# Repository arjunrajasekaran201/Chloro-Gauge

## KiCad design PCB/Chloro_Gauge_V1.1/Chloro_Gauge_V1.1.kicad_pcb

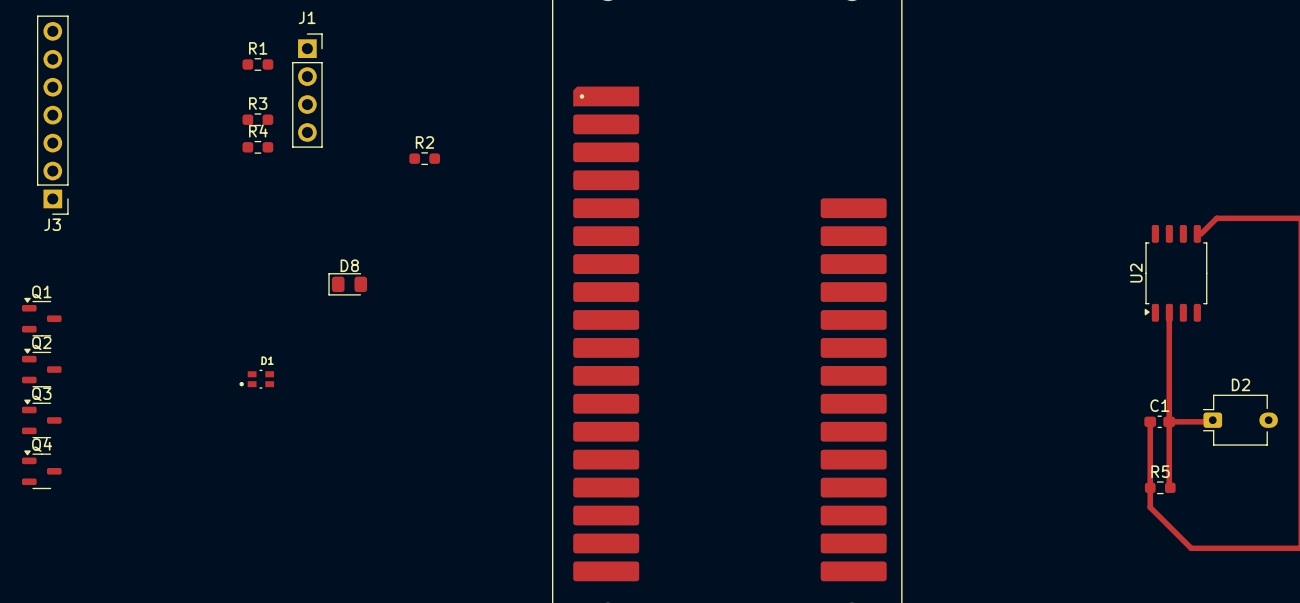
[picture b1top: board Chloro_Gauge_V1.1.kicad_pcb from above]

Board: 2 copper layers, 17 parts (0 on the bottom side), 19 nets.

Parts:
C1: 100nF; C_0603_1608Metric_Pad1.08x0.95mm_HandSolder
D1: Everlight_RGB_19-237_R6GHBHC-A01_2T; LED_19-237_R6GHBHC-A01_2T
D2: BPW34; Osram_DIL2_4.3x4.65mm_P5.08mm
D8: NIR; LED_0805_2012Metric_Pad1.15x1.40mm_HandSolder
J1: DISPLAY; PinSocket_1x04_P2.54mm_Vertical
J3: COLOUR SENSOR; PinHeader_1x07_P2.54mm_Vertical
Q1, Q2, Q3, Q4: BC547; SOT-23-3
R1, R2, R3, R4: 1k; R_0603_1608Metric_Pad0.98x0.95mm_HandSolder
R5: 10k; R_0603_1608Metric_Pad0.98x0.95mm_HandSolder
U1: DFR0654; MODULE_DFR0654
U2: UA741CN; SOIC-8_5.3x5.3mm_P1.27mm

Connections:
+3.3V: D1.4, D8.2 (A), J1.2, J3.5, U1.2 (3.3V), U1.31 (3.3V), U2.3 (V+)
BLUE_D10: R3.1, U1.21 (D12)
CLRSNS_INT_D9: J3.2, U1.11 (D9)
GND: D2.2 (A), J1.1, J3.6, Q1.3 (E), Q2.3 (E), Q3.3 (E), Q4.3 (E), U1.4 (GND), U1.30 (GND), U2.1 (+), U2.4 (V-)
GREEN_D11: R2.1, U1.20 (D11)
NIR_D13: R4.2, U1.22 (D13)
unnamed: C1.2, D2.1 (K), R5.2, U2.2 (-)
unnamed: D8.1 (K), Q4.1 (C)
unnamed: Q1.2 (B), R1.2
unnamed: D1.1, Q1.1 (C)
unnamed: Q2.2 (B), R2.2
unnamed: D1.2, Q2.1 (C)
unnamed: Q3.2 (B), R3.2
unnamed: D1.3, Q3.1 (C)
unnamed: Q4.2 (B), R4.1
PHOTODIODE_ADC_A0: C1.1, R5.1, U1.23 (A0), U2.5
RED_D12: R1.1, U1.19 (D10)
SCL: J1.3, J3.4, U1.9 (SCL), U1.29 (SCL)
SDA: J1.4, J3.3, U1.10 (SDA), U1.28 (SDA)

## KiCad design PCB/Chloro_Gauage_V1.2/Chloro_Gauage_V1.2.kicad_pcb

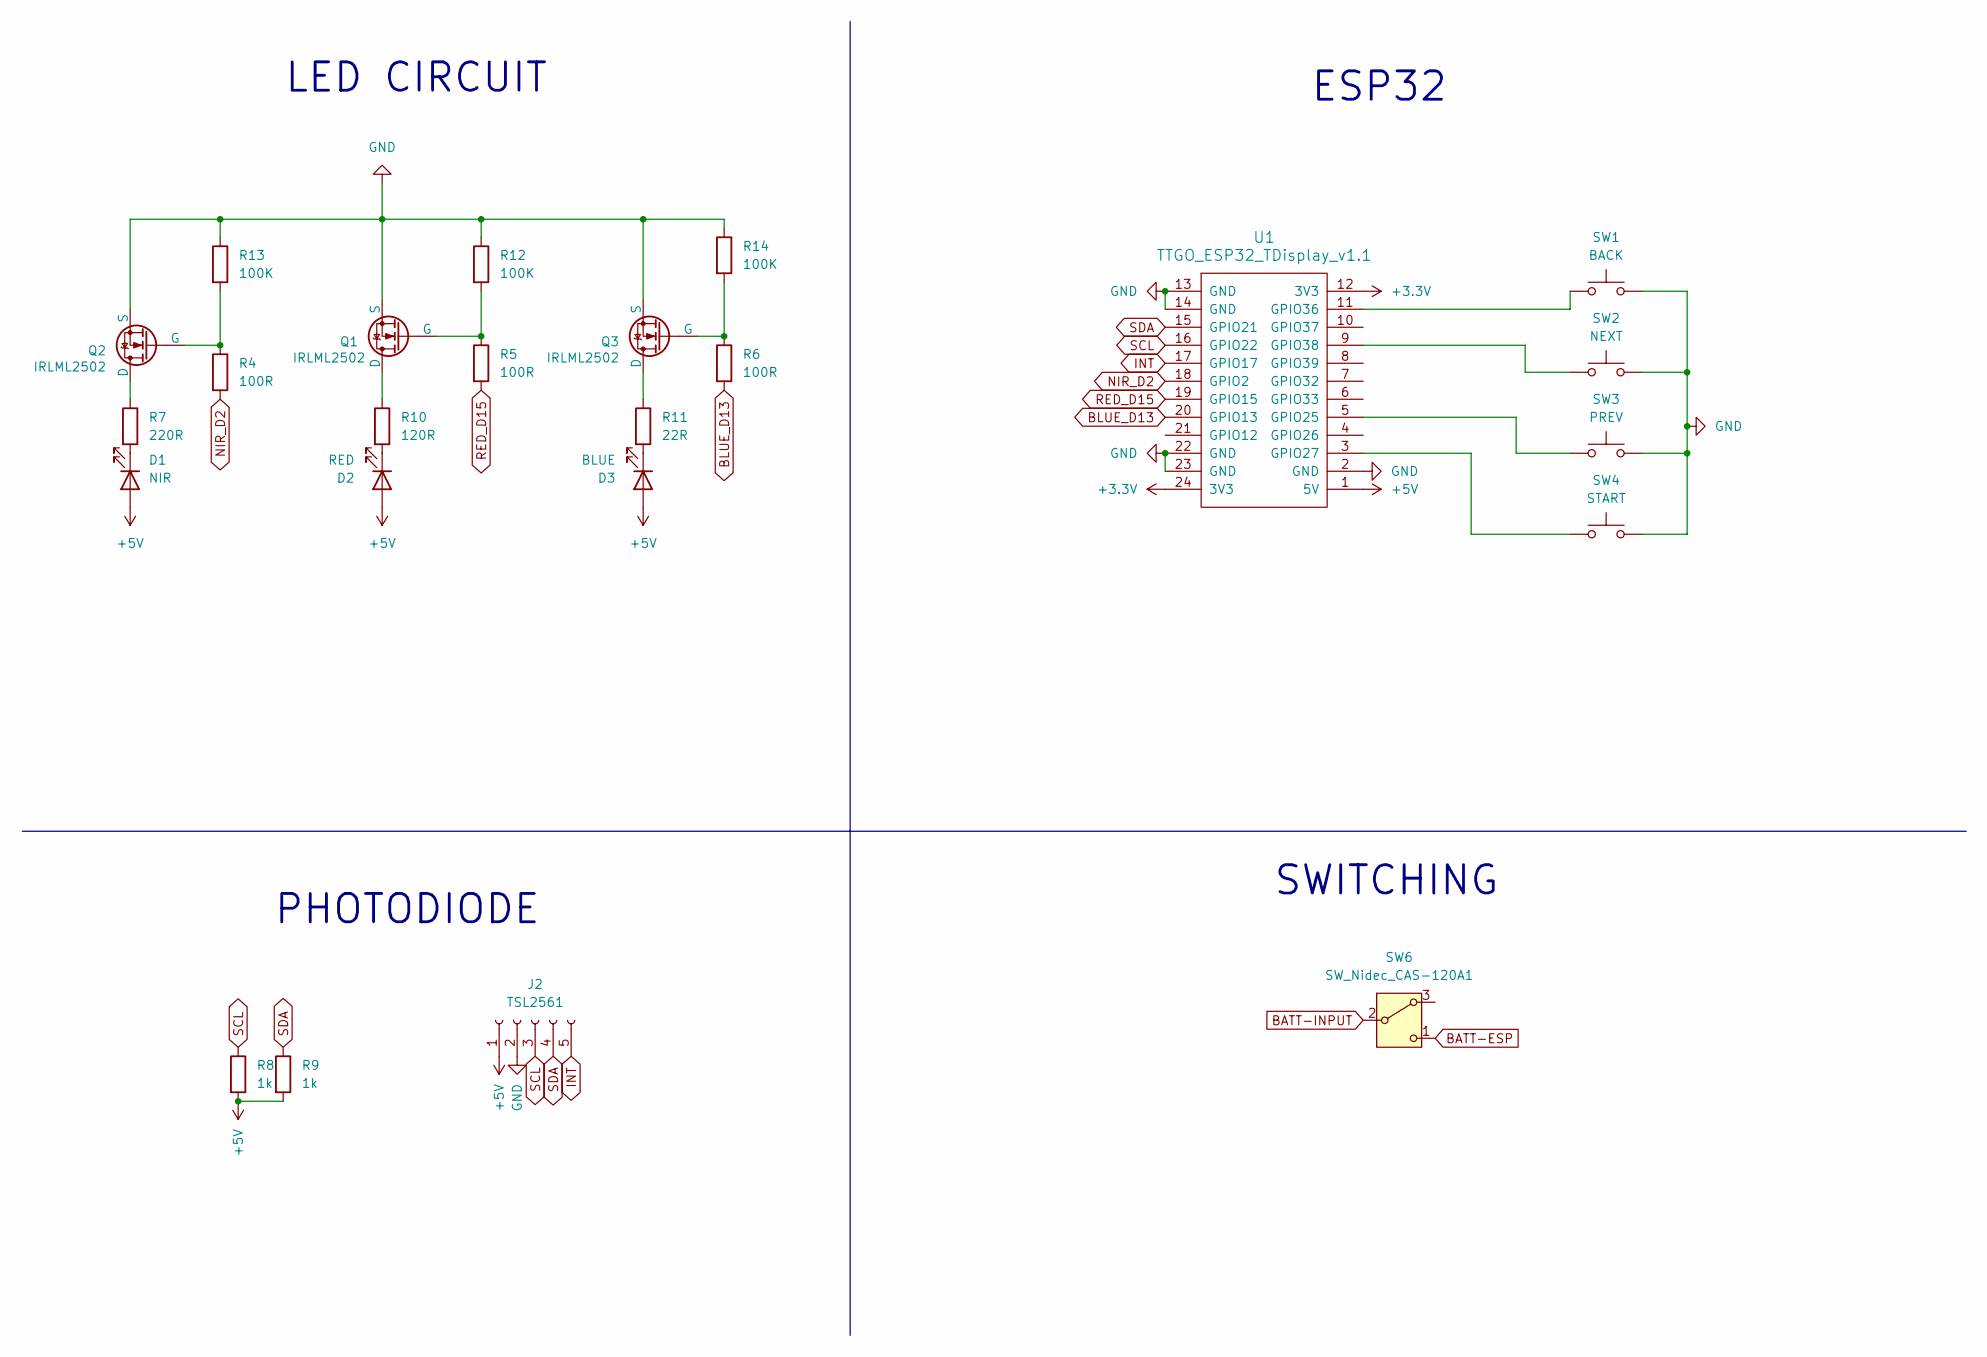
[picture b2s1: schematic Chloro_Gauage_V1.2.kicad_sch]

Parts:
D1: NIR; LED_0805_2012Metric_Pad1.15x1.40mm_HandSolder
D2: RED; LED_1206_3216Metric_Pad1.42x1.75mm_HandSolder
D3: BLUE; LED_1206_3216Metric_Pad1.42x1.75mm_HandSolder
J2: TSL2561; PinSocket_1x05_P2.54mm_Vertical
Q1, Q2, Q3: IRLML2502; TSOT-23
R4, R5, R6: 100R; R_1206_3216Metric_Pad1.30x1.75mm_HandSolder
R7: 220R; R_1206_3216Metric_Pad1.30x1.75mm_HandSolder
R8, R9: 1k; R_1206_3216Metric_Pad1.30x1.75mm_HandSolder
R10: 120R; R_1206_3216Metric_Pad1.30x1.75mm_HandSolder
R11: 22R; R_1206_3216Metric_Pad1.30x1.75mm_HandSolder
R12, R13, R14: 100K; R_1206_3216Metric_Pad1.30x1.75mm_HandSolder
SW1: BACK; SW_SPST_Omron_B3FS-105xP
SW2: NEXT; SW_SPST_Omron_B3FS-105xP
SW3: PREV; SW_SPST_Omron_B3FS-105xP
SW4: START; SW_SPST_Omron_B3FS-105xP
SW6: SW_Nidec_CAS-120A1; SW_DIP_SPSTx01_Slide_Copal_CVS-01xB_W5.9mm_P1mm
U1: TTGO_ESP32_TDisplay_v1.1

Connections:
+3.3V: U1.12 (3V3), U1.24 (3V3)
+5V: D1.2 (A), D2.2 (A), D3.2 (A), J2.1, R8.2, R9.2, U1.1 (5V)
BATT-ESP: SW6.1 (C)
BATT-INPUT: SW6.2 (B)
BLUE_D13: R6.2, U1.20 (GPIO13)
GND: J2.2, Q1.2 (S), Q2.2 (S), Q3.2 (S), R12.1, R13.1, R14.1, SW1.2, SW2.2, SW3.2, SW4.2, U1.2 (GND), U1.13 (GND), U1.14 (GND), U1.22 (GND), U1.23 (GND)
INT: J2.5, U1.17 (GPIO17)
NIR_D2: R4.2, U1.18 (GPIO2)
unnamed: D1.1 (K), R7.2
unnamed: D2.1 (K), R10.2
unnamed: D3.1 (K), R11.2
unnamed: Q1.3 (D), R10.1
unnamed: Q1.1 (G), R5.1, R12.2
unnamed: Q2.3 (D), R7.1
unnamed: Q2.1 (G), R4.1, R13.2
unnamed: Q3.3 (D), R11.1
unnamed: Q3.1 (G), R6.1, R14.2
unnamed: SW3.1, U1.5 (GPIO25)
unnamed: SW4.1, U1.3 (GPIO27)
unnamed: SW1.1, U1.11 (GPIO36)
unnamed: SW2.1, U1.9 (GPIO38)
RED_D15: R5.2, U1.19 (GPIO15)
SCL: J2.3, R8.1, U1.16 (GPIO22)
SDA: J2.4, R9.1, U1.15 (GPIO21)

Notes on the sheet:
SWITCHING
PHOTODIODE
LED CIRCUIT
ESP32

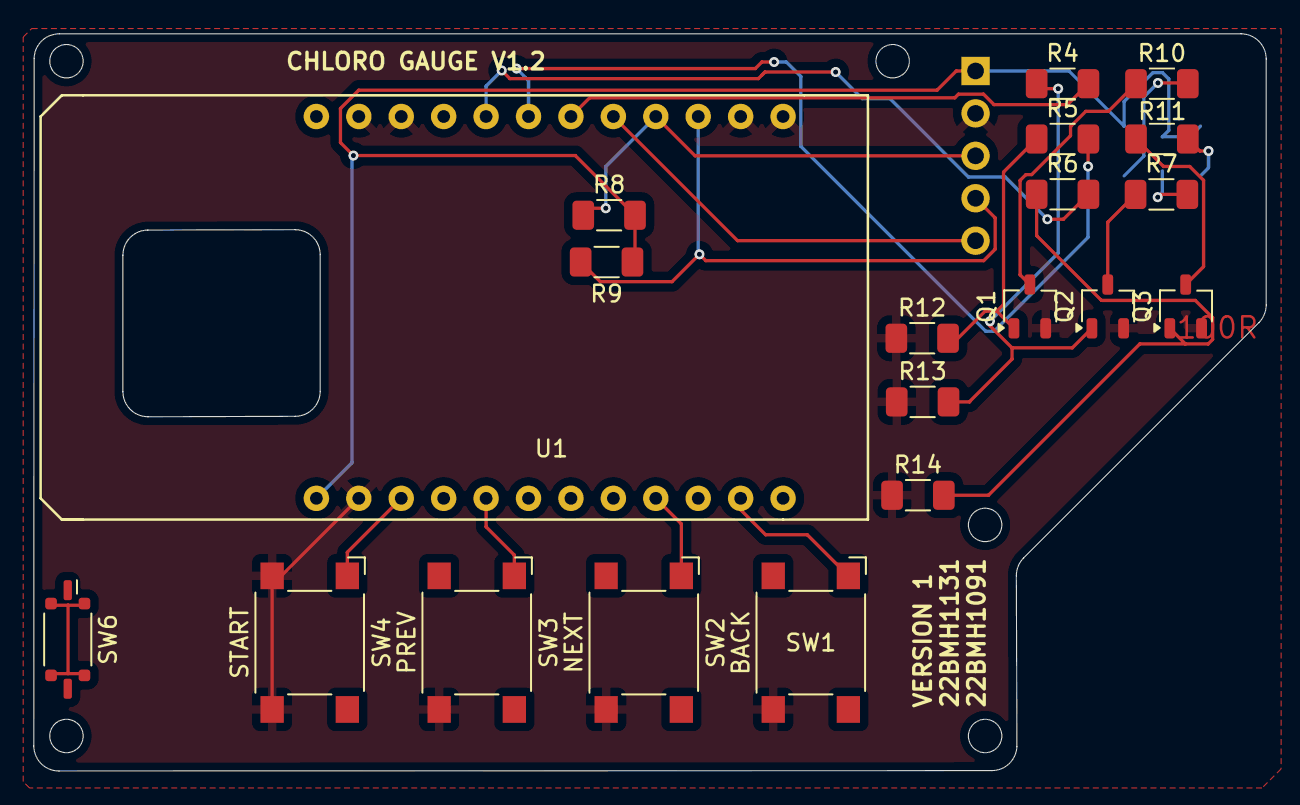
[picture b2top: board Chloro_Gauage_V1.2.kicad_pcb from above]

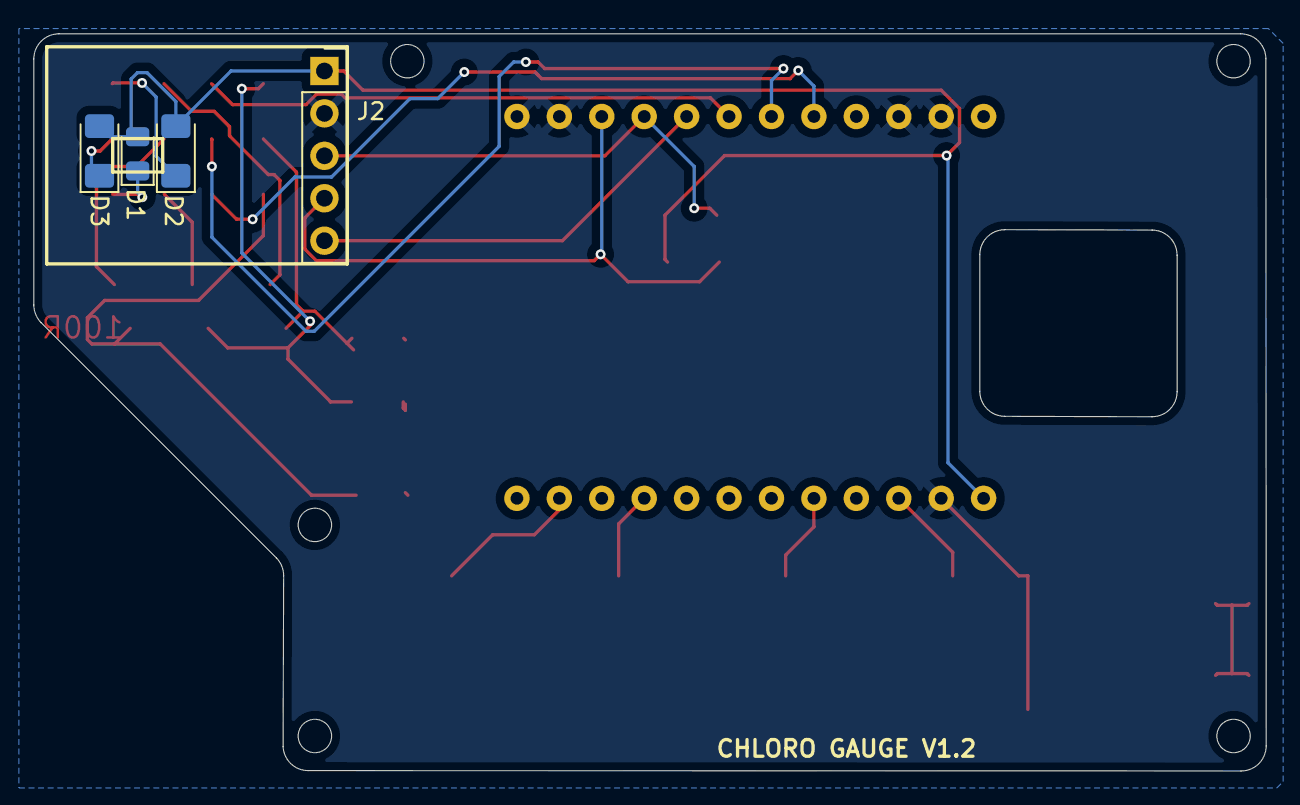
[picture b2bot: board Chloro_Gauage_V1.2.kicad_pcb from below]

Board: 2 copper layers, 73.8 x 44.1 mm, 24 parts (4 on the bottom side), 21 nets.

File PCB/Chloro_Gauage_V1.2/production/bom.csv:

Designator,Footprint,Quantity,Value,LCSC Part #
D1,0805,1,NIR,
D2,1206,1,RED,
D3,1206,1,BLUE,
J2,PinSocket_1x05_P2.54mm_Vertical,1,TSL2561,
"Q1, Q2, Q3",TSOT-23,3,IRLML2502,
R10,1206,1,120R,
R11,1206,1,22R,
"R12, R13, R14",1206,3,100K,
"R4, R5, R6",1206,3,100R,
R7,1206,1,220R,
"R8, R9",1206,2,1k,
SW1,SW_SPST_Omron_B3FS-105xP,1,BACK,
SW2,SW_SPST_Omron_B3FS-105xP,1,NEXT,
SW3,SW_SPST_Omron_B3FS-105xP,1,PREV,
SW4,SW_SPST_Omron_B3FS-105xP,1,START,
SW6,SW_DIP_SPSTx01_Slide_Copal_CVS-01xB_W5.9mm_P1mm,1,SW_Nidec_CAS-120A1,
U1,TTGO_ESP32_TDisplay_v1.1,1,TTGO_ESP32_TDisplay_v1.1,

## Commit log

2025-10-29 Create CAD Designs
